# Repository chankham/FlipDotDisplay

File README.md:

# FlipDotDisplay
Code for flip dot display

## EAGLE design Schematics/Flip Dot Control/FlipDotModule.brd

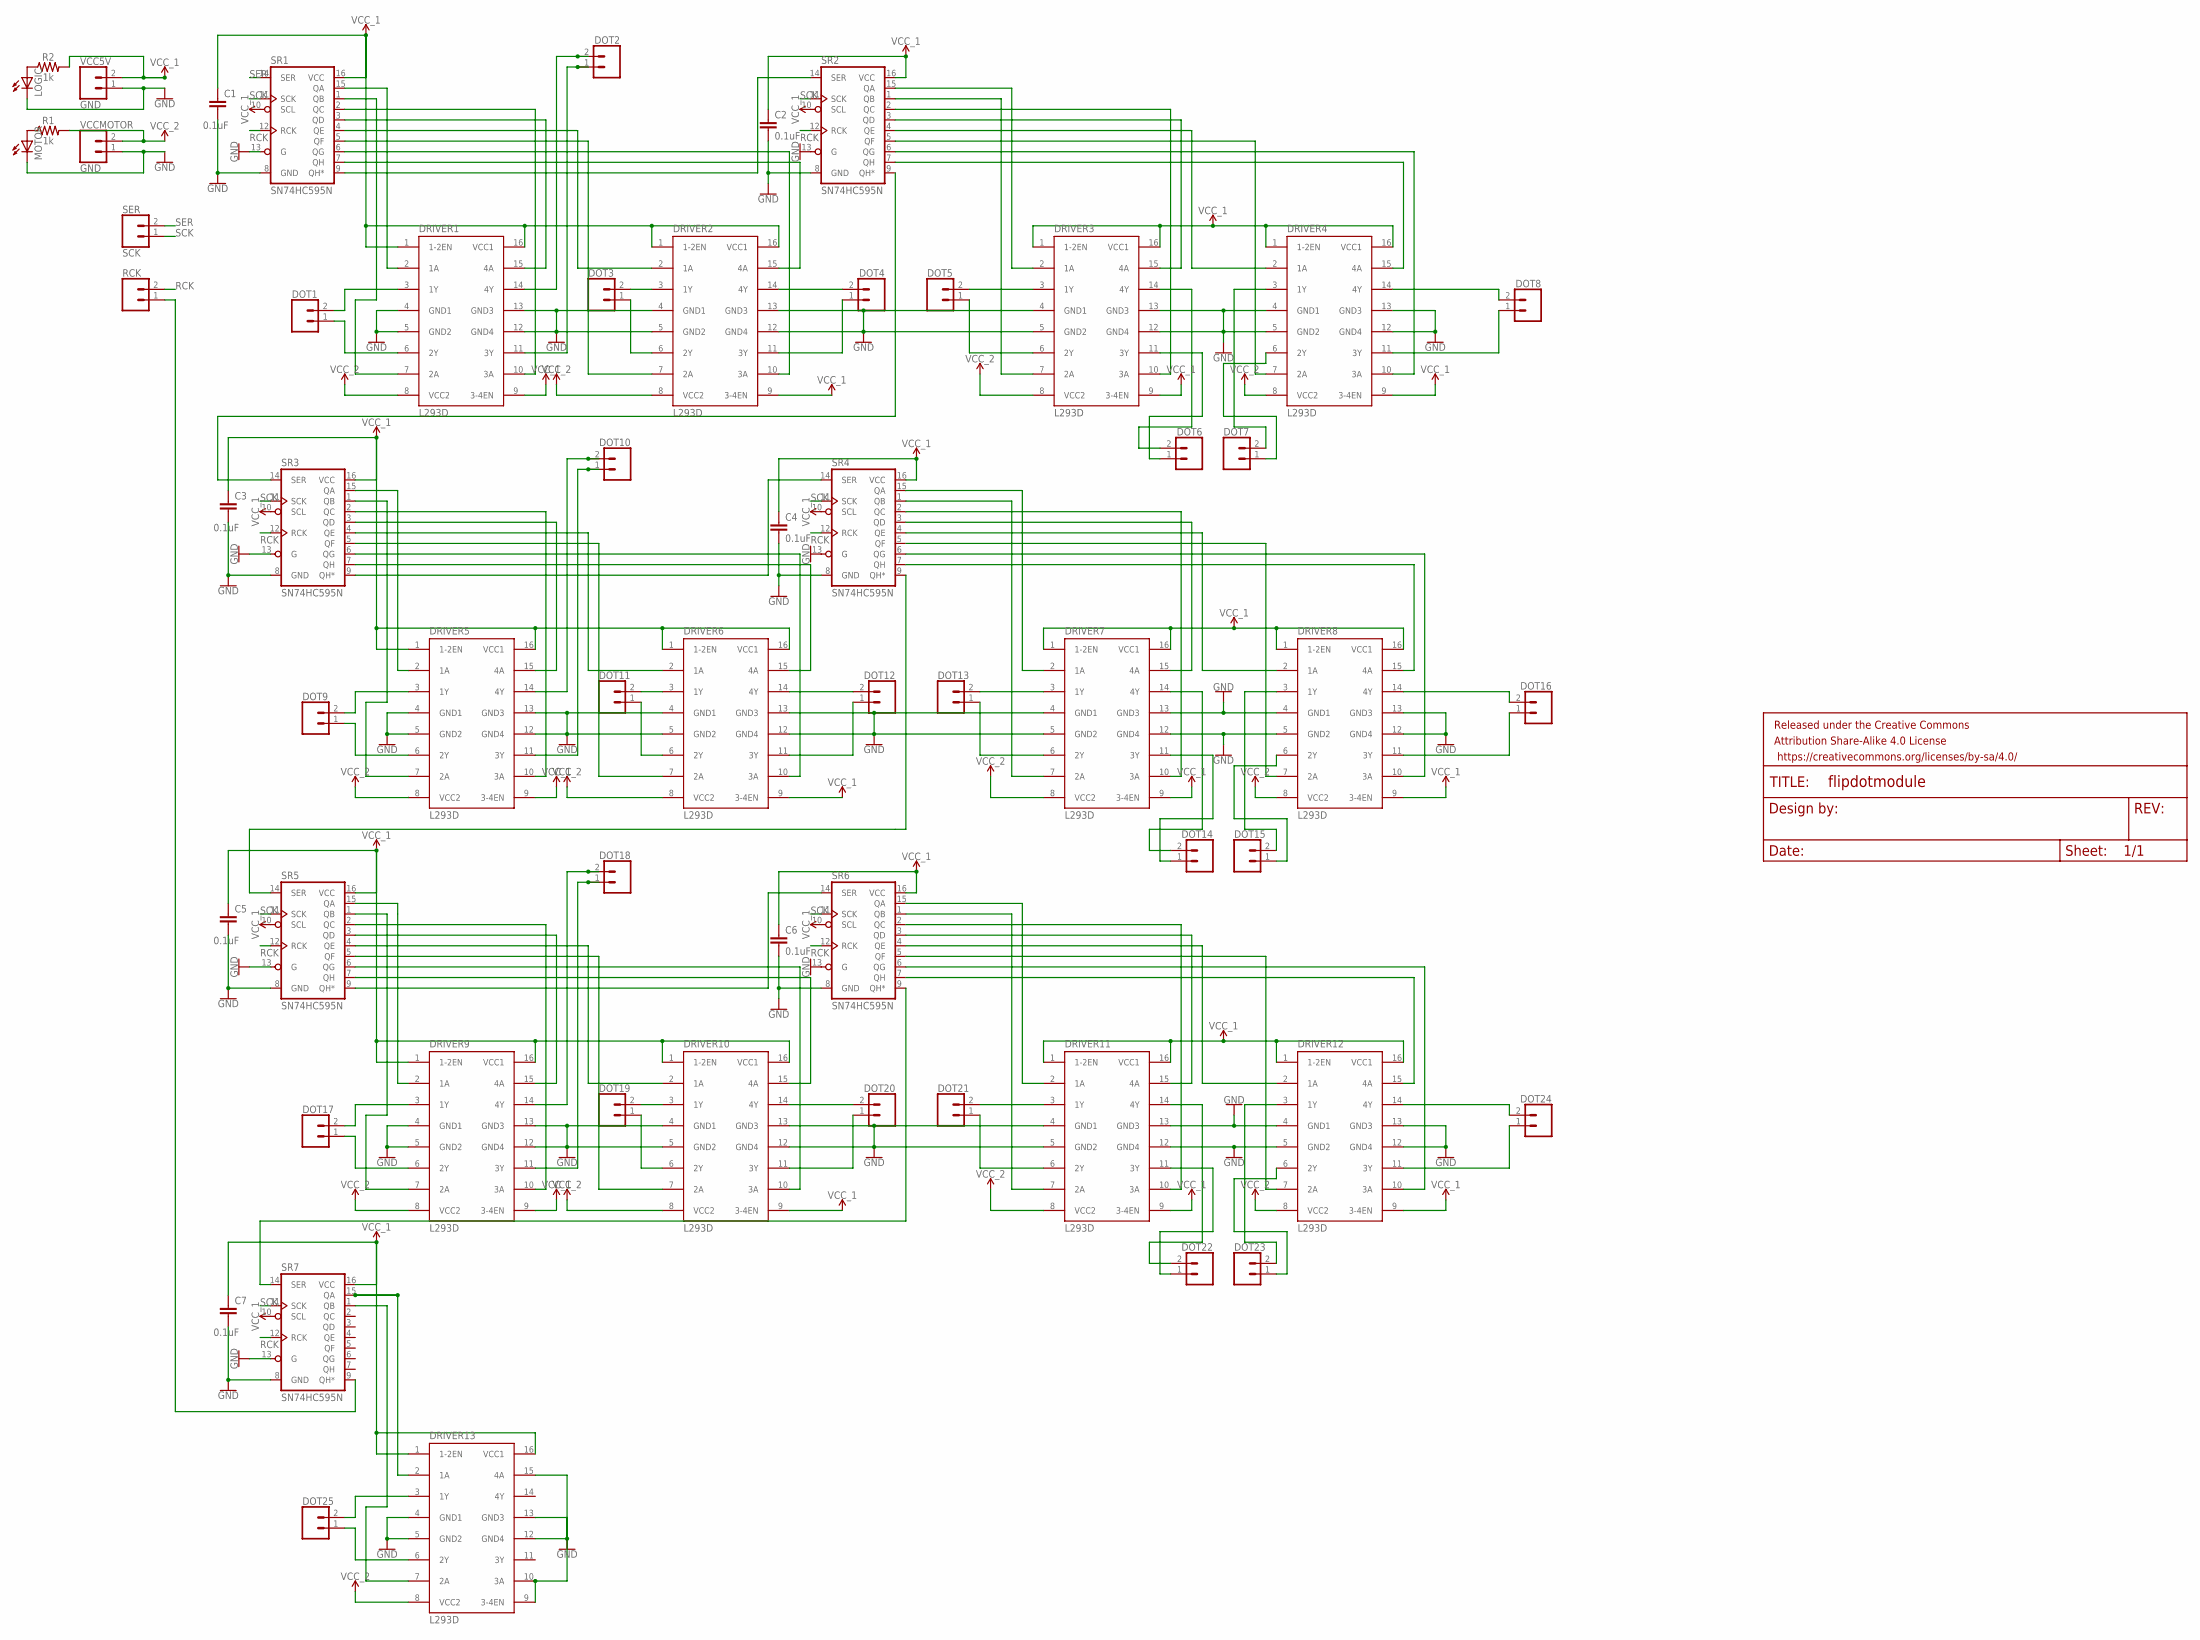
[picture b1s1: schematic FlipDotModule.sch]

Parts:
C1, C2, C3, C4, C5, C6, C7: 0.1uF; CAP-PTH-SMALL-KIT
DOT1, DOT2, DOT3, DOT4, DOT5, DOT6, DOT7, DOT8, DOT9, DOT10, DOT11, DOT12, DOT13, DOT14, DOT15, DOT16, DOT17, DOT18, DOT19, DOT20, DOT21, DOT22, DOT23, DOT24, DOT25: CONN_025MM; SCREWTERMINAL-5MM-2
DRIVER1, DRIVER2, DRIVER3, DRIVER4, DRIVER5, DRIVER6, DRIVER7, DRIVER8, DRIVER9, DRIVER10, DRIVER11, DRIVER12, DRIVER13: L293D; DIL16
FRAME1: FRAME-LETTERNO_PACKAGE; DUMMY
LOGIC: LED3MM
MOTOR: LED3MM
R1, R2: 1k; AXIAL-0.3
RCK: CONN_025MM; SCREWTERMINAL-5MM-2
SER: SCK; SCREWTERMINAL-5MM-2
SR1, SR2, SR3, SR4, SR5, SR6, SR7: SN74HC595N; DIP16
VCC5V: GND; SCREWTERMINAL-5MM-2
VCCMOTOR: GND; SCREWTERMINAL-5MM-2

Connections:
GND: C1.2, C2.2, C3.2, C4.2, C5.2, C6.2, C7.2, DRIVER1.4 (GND1), DRIVER1.5 (GND2), DRIVER1.12 (GND4), DRIVER1.13 (GND3), DRIVER2.4 (GND1), DRIVER2.5 (GND2), DRIVER2.12 (GND4), DRIVER2.13 (GND3), DRIVER3.4 (GND1), DRIVER3.5 (GND2), DRIVER3.12 (GND4), DRIVER3.13 (GND3), DRIVER4.4 (GND1), DRIVER4.5 (GND2), DRIVER4.12 (GND4), DRIVER4.13 (GND3), DRIVER5.4 (GND1), DRIVER5.5 (GND2), DRIVER5.12 (GND4), DRIVER5.13 (GND3), DRIVER6.4 (GND1), DRIVER6.5 (GND2), DRIVER6.12 (GND4), DRIVER6.13 (GND3), DRIVER7.4 (GND1), DRIVER7.5 (GND2), DRIVER7.12 (GND4), DRIVER7.13 (GND3), DRIVER8.4 (GND1), DRIVER8.5 (GND2), DRIVER8.12 (GND4), DRIVER8.13 (GND3), DRIVER9.4 (GND1), DRIVER9.5 (GND2), DRIVER9.12 (GND4), DRIVER9.13 (GND3), DRIVER10.4 (GND1), DRIVER10.5 (GND2), DRIVER10.12 (GND4), DRIVER10.13 (GND3), DRIVER11.4 (GND1), DRIVER11.5 (GND2), DRIVER11.12 (GND4), DRIVER11.13 (GND3), DRIVER12.4 (GND1), DRIVER12.5 (GND2), DRIVER12.12 (GND4), DRIVER12.13 (GND3), DRIVER13.4 (GND1), DRIVER13.5 (GND2), DRIVER13.9 (3-4EN), DRIVER13.10 (3A), DRIVER13.12 (GND4), DRIVER13.13 (GND3), DRIVER13.15 (4A), LOGIC.K (C), MOTOR.K (C), SR1.8 (GND), SR1.13 (G), SR2.8 (GND), SR2.13 (G), SR3.8 (GND), SR3.13 (G), SR4.8 (GND), SR4.13 (G), SR5.8 (GND), SR5.13 (G), SR6.8 (GND), SR6.13 (G), SR7.8 (GND), SR7.13 (G), VCC5V.1, VCCMOTOR.1
unnamed: SR1.9 (QH*), SR2.14 (SER)
unnamed: DOT5.2, DRIVER3.3 (1Y)
unnamed: MOTOR.A, R1.P$1 (1)
unnamed: DRIVER1.7 (2A), SR1.1 (QB)
unnamed: SR3.9 (QH*), SR4.14 (SER)
unnamed: LOGIC.A, R2.P$1 (1)
unnamed: DRIVER1.10 (3A), SR1.2 (QC)
unnamed: DRIVER1.15 (4A), SR1.3 (QD)
unnamed: DRIVER2.2 (1A), SR1.4 (QE)
unnamed: DRIVER2.7 (2A), SR1.5 (QF)
unnamed: DRIVER2.10 (3A), SR1.6 (QG)
unnamed: DRIVER2.15 (4A), SR1.7 (QH)
unnamed: DRIVER1.2 (1A), SR1.15 (QA)
unnamed: DRIVER5.7 (2A), SR3.1 (QB)
unnamed: DRIVER3.2 (1A), SR2.15 (QA)
unnamed: DRIVER3.7 (2A), SR2.1 (QB)
unnamed: DRIVER3.10 (3A), SR2.2 (QC)
unnamed: DRIVER3.15 (4A), SR2.3 (QD)
unnamed: DRIVER4.2 (1A), SR2.4 (QE)
unnamed: DRIVER4.7 (2A), SR2.5 (QF)
unnamed: DRIVER4.10 (3A), SR2.6 (QG)
unnamed: DRIVER4.15 (4A), SR2.7 (QH)
unnamed: DOT1.2, DRIVER1.3 (1Y)
unnamed: DOT4.2, DRIVER2.14 (4Y)
unnamed: DOT2.1, DRIVER1.11 (3Y)
unnamed: DOT1.1, DRIVER1.6 (2Y)
unnamed: DOT3.2, DRIVER2.3 (1Y)
unnamed: DOT3.1, DRIVER2.6 (2Y)
unnamed: DOT2.2, DRIVER1.14 (4Y)
unnamed: DOT4.1, DRIVER2.11 (3Y)
unnamed: DOT5.1, DRIVER3.6 (2Y)
unnamed: DOT6.2, DRIVER3.14 (4Y)
unnamed: DOT6.1, DRIVER3.11 (3Y)
unnamed: DOT7.2, DRIVER4.3 (1Y)
unnamed: DOT7.1, DRIVER4.6 (2Y)
unnamed: DOT8.2, DRIVER4.14 (4Y)
unnamed: DOT8.1, DRIVER4.11 (3Y)
unnamed: DRIVER5.10 (3A), SR3.2 (QC)
unnamed: DRIVER5.15 (4A), SR3.3 (QD)
unnamed: DRIVER6.2 (1A), SR3.4 (QE)
unnamed: DRIVER6.7 (2A), SR3.5 (QF)
unnamed: DRIVER6.10 (3A), SR3.6 (QG)
unnamed: DRIVER6.15 (4A), SR3.7 (QH)
unnamed: DRIVER5.2 (1A), SR3.15 (QA)
unnamed: DRIVER7.2 (1A), SR4.15 (QA)
unnamed: DRIVER7.7 (2A), SR4.1 (QB)
unnamed: DRIVER7.10 (3A), SR4.2 (QC)
unnamed: DRIVER7.15 (4A), SR4.3 (QD)
unnamed: DRIVER8.2 (1A), SR4.4 (QE)
unnamed: DRIVER8.7 (2A), SR4.5 (QF)
unnamed: DRIVER8.10 (3A), SR4.6 (QG)
unnamed: DRIVER8.15 (4A), SR4.7 (QH)
unnamed: DOT10.1, DRIVER5.11 (3Y)
unnamed: DOT9.2, DRIVER5.3 (1Y)
unnamed: DOT9.1, DRIVER5.6 (2Y)
unnamed: DOT11.2, DRIVER6.3 (1Y)
unnamed: DOT11.1, DRIVER6.6 (2Y)
unnamed: DOT10.2, DRIVER5.14 (4Y)
unnamed: DOT12.2, DRIVER6.14 (4Y)
unnamed: DOT12.1, DRIVER6.11 (3Y)
unnamed: DOT13.2, DRIVER7.3 (1Y)
unnamed: DOT13.1, DRIVER7.6 (2Y)
unnamed: DOT14.2, DRIVER7.14 (4Y)
unnamed: DOT14.1, DRIVER7.11 (3Y)
unnamed: DOT15.2, DRIVER8.3 (1Y)
unnamed: DOT15.1, DRIVER8.6 (2Y)
unnamed: DOT16.2, DRIVER8.14 (4Y)
unnamed: DOT16.1, DRIVER8.11 (3Y)
unnamed: SR5.9 (QH*), SR6.14 (SER)
unnamed: DRIVER9.2 (1A), SR5.15 (QA)
unnamed: DRIVER9.7 (2A), SR5.1 (QB)
unnamed: DRIVER9.10 (3A), SR5.2 (QC)
unnamed: DRIVER9.15 (4A), SR5.3 (QD)
unnamed: DRIVER10.2 (1A), SR5.4 (QE)
unnamed: DRIVER10.7 (2A), SR5.5 (QF)
unnamed: DRIVER10.10 (3A), SR5.6 (QG)
unnamed: DRIVER10.15 (4A), SR5.7 (QH)
unnamed: DRIVER11.2 (1A), SR6.15 (QA)
unnamed: DRIVER11.7 (2A), SR6.1 (QB)
unnamed: DRIVER11.10 (3A), SR6.2 (QC)
unnamed: DRIVER11.15 (4A), SR6.3 (QD)
unnamed: DRIVER12.2 (1A), SR6.4 (QE)
unnamed: DRIVER12.7 (2A), SR6.5 (QF)
unnamed: DRIVER12.10 (3A), SR6.6 (QG)
unnamed: DRIVER12.15 (4A), SR6.7 (QH)
unnamed: DOT18.1, DRIVER9.11 (3Y)
unnamed: DOT17.2, DRIVER9.3 (1Y)
unnamed: DOT17.1, DRIVER9.6 (2Y)
unnamed: DOT19.2, DRIVER10.3 (1Y)
unnamed: DOT19.1, DRIVER10.6 (2Y)
unnamed: DOT18.2, DRIVER9.14 (4Y)
unnamed: DOT20.2, DRIVER10.14 (4Y)
unnamed: DOT20.1, DRIVER10.11 (3Y)
unnamed: DOT21.2, DRIVER11.3 (1Y)
unnamed: DOT21.1, DRIVER11.6 (2Y)
unnamed: DOT22.2, DRIVER11.14 (4Y)
unnamed: DOT22.1, DRIVER11.11 (3Y)
unnamed: DOT23.2, DRIVER12.3 (1Y)
unnamed: DOT23.1, DRIVER12.6 (2Y)
unnamed: DOT24.2, DRIVER12.14 (4Y)
unnamed: DOT24.1, DRIVER12.11 (3Y)
unnamed: RCK.1, SR7.9 (QH*)
unnamed: DRIVER13.2 (1A), SR7.15 (QA)
unnamed: DRIVER13.7 (2A), SR7.1 (QB)
unnamed: DOT25.2, DRIVER13.3 (1Y)
unnamed: DOT25.1, DRIVER13.6 (2Y)
unnamed: SR2.9 (QH*), SR3.14 (SER)
unnamed: SR4.9 (QH*), SR5.14 (SER)
unnamed: SR6.9 (QH*), SR7.14 (SER)
RCK: RCK.2, SR1.12 (RCK), SR2.12 (RCK), SR3.12 (RCK), SR4.12 (RCK), SR5.12 (RCK), SR6.12 (RCK), SR7.12 (RCK)
SCK: SER.1, SR1.11 (SCK), SR2.11 (SCK), SR3.11 (SCK), SR4.11 (SCK), SR5.11 (SCK), SR6.11 (SCK), SR7.11 (SCK)
SER: SER.2, SR1.14 (SER)
VCC_1: C1.1, C2.1, C3.1, C4.1, C5.1, C6.1, C7.1, DRIVER1.1 (1-2EN), DRIVER1.9 (3-4EN), DRIVER1.16 (VCC1), DRIVER2.1 (1-2EN), DRIVER2.9 (3-4EN), DRIVER2.16 (VCC1), DRIVER3.1 (1-2EN), DRIVER3.9 (3-4EN), DRIVER3.16 (VCC1), DRIVER4.1 (1-2EN), DRIVER4.9 (3-4EN), DRIVER4.16 (VCC1), DRIVER5.1 (1-2EN), DRIVER5.9 (3-4EN), DRIVER5.16 (VCC1), DRIVER6.1 (1-2EN), DRIVER6.9 (3-4EN), DRIVER6.16 (VCC1), DRIVER7.1 (1-2EN), DRIVER7.9 (3-4EN), DRIVER7.16 (VCC1), DRIVER8.1 (1-2EN), DRIVER8.9 (3-4EN), DRIVER8.16 (VCC1), DRIVER9.1 (1-2EN), DRIVER9.9 (3-4EN), DRIVER9.16 (VCC1), DRIVER10.1 (1-2EN), DRIVER10.9 (3-4EN), DRIVER10.16 (VCC1), DRIVER11.1 (1-2EN), DRIVER11.9 (3-4EN), DRIVER11.16 (VCC1), DRIVER12.1 (1-2EN), DRIVER12.9 (3-4EN), DRIVER12.16 (VCC1), DRIVER13.1 (1-2EN), DRIVER13.16 (VCC1), R2.P$2 (2), SR1.10 (SCL), SR1.16 (VCC), SR2.10 (SCL), SR2.16 (VCC), SR3.10 (SCL), SR3.16 (VCC), SR4.10 (SCL), SR4.16 (VCC), SR5.10 (SCL), SR5.16 (VCC), SR6.10 (SCL), SR6.16 (VCC), SR7.10 (SCL), SR7.16 (VCC), VCC5V.2
VCC_2: DRIVER1.8 (VCC2), DRIVER2.8 (VCC2), DRIVER3.8 (VCC2), DRIVER4.8 (VCC2), DRIVER5.8 (VCC2), DRIVER6.8 (VCC2), DRIVER7.8 (VCC2), DRIVER8.8 (VCC2), DRIVER9.8 (VCC2), DRIVER10.8 (VCC2), DRIVER11.8 (VCC2), DRIVER12.8 (VCC2), DRIVER13.8 (VCC2), R1.P$2 (2), VCCMOTOR.2

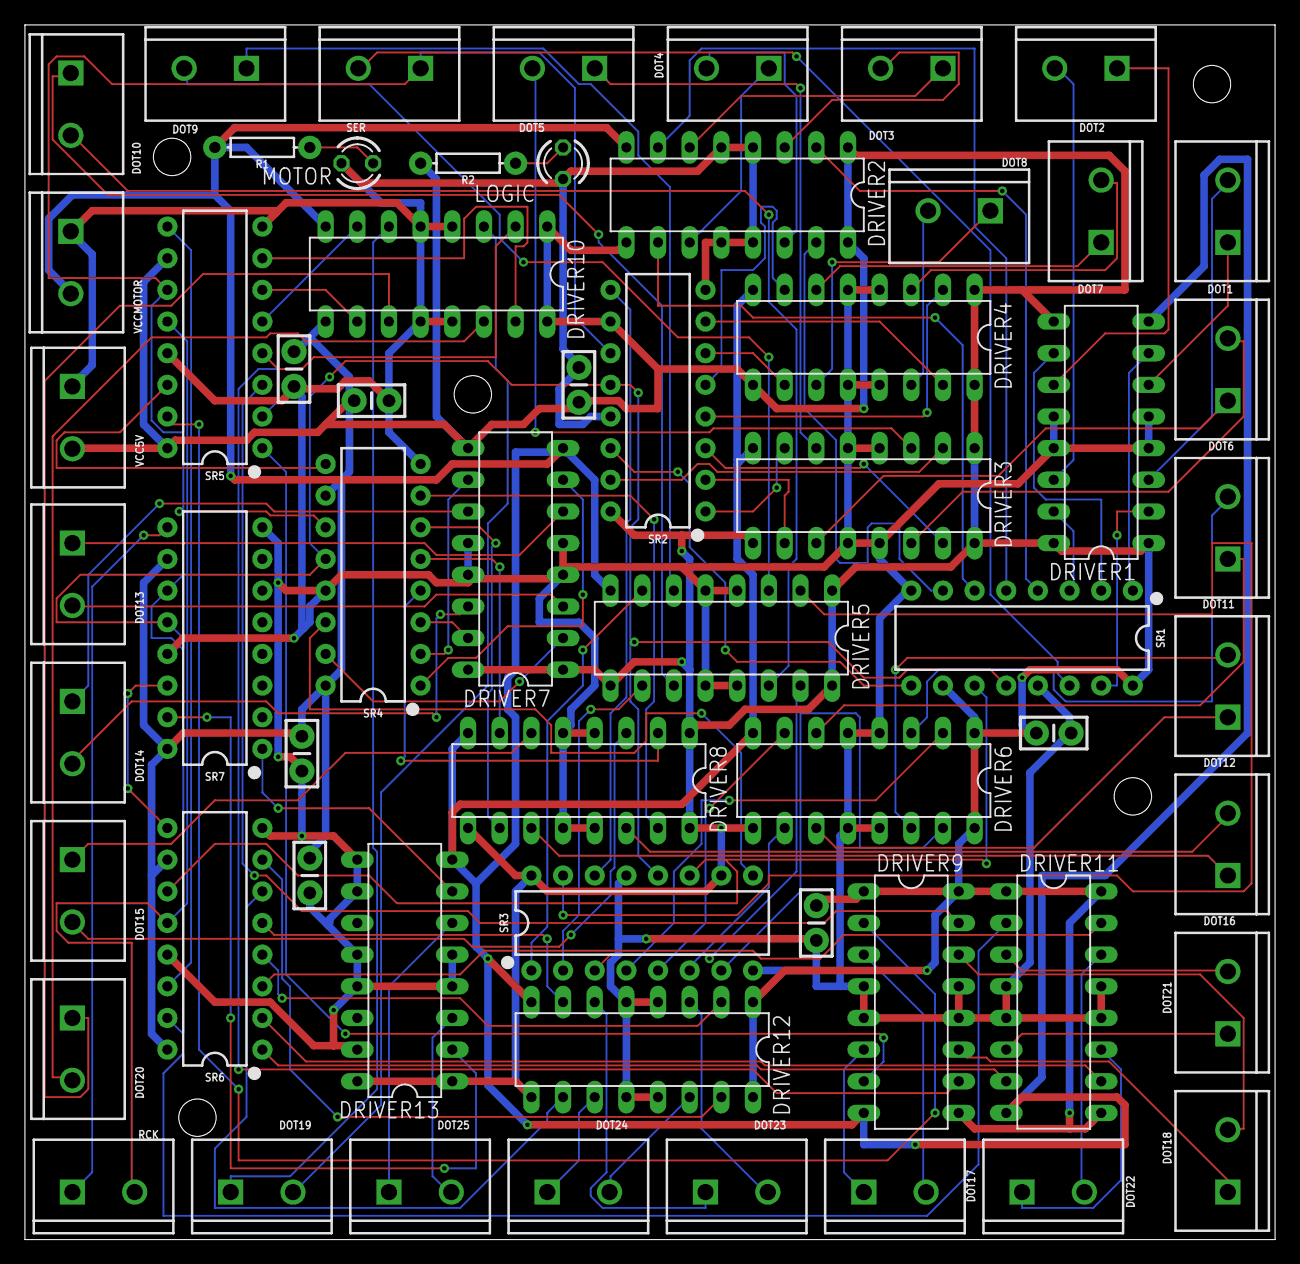
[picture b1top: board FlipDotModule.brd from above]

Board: 2 copper layers, 100.3 x 97.5 mm, 61 parts (0 on the bottom side), 115 nets.

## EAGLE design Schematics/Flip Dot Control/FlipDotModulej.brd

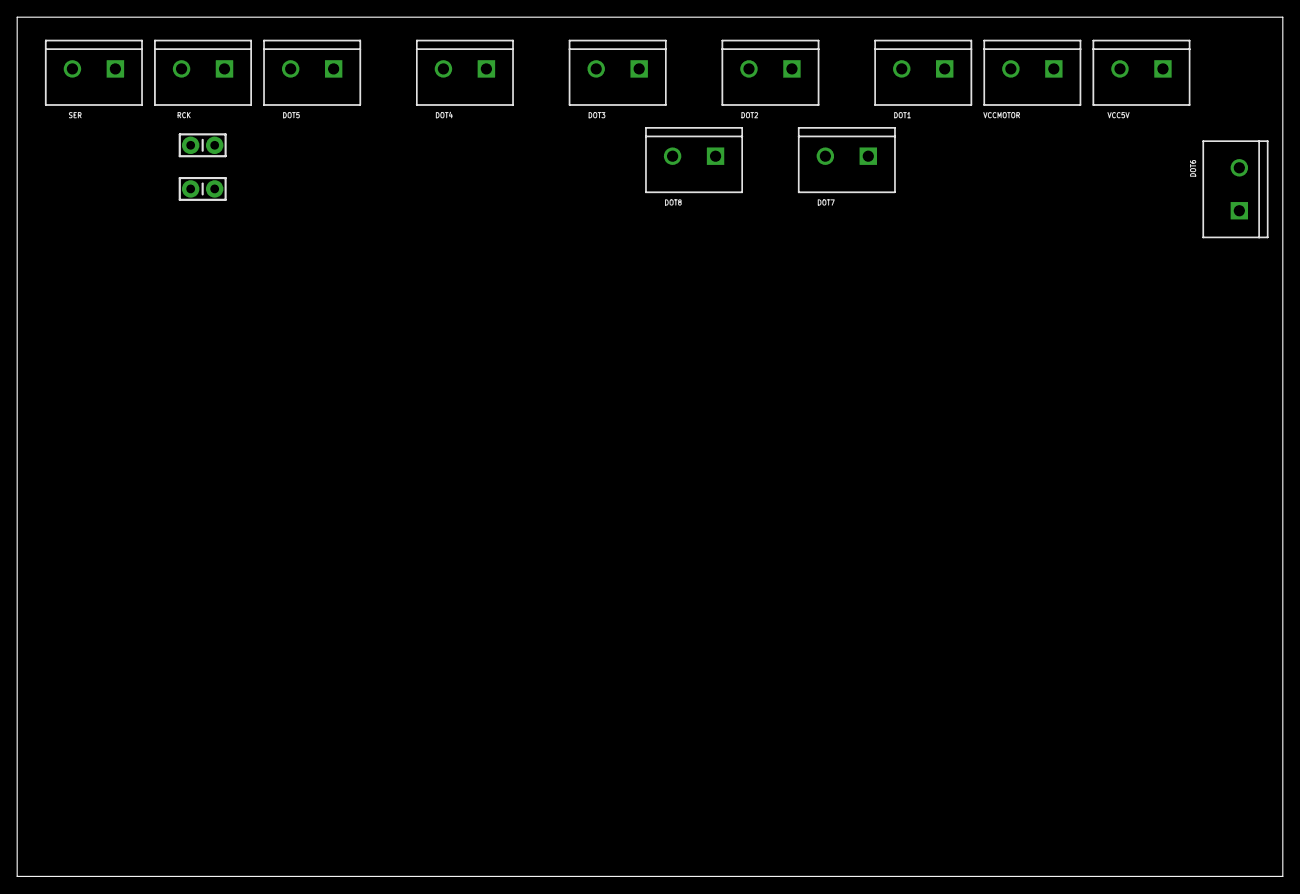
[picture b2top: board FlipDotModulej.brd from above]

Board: 2 copper layers, 147.3 x 100.0 mm, 15 parts (0 on the bottom side), 2 nets, no tracks yet.

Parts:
C1, C2: 0.1uF; CAP-PTH-SMALL-KIT
DOT1, DOT2, DOT3, DOT4, DOT5, DOT6, DOT7, DOT8: SCREWTERMINAL-5MM-2
FRAME1: FRAME-LETTERNO_PACKAGE; DUMMY
RCK: SCREWTERMINAL-5MM-2
SER: SCK; SCREWTERMINAL-5MM-2
VCC5V: GND; SCREWTERMINAL-5MM-2
VCCMOTOR: GND; SCREWTERMINAL-5MM-2

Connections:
GND: C1.2, C2.2, RCK.1, VCC5V.1, VCCMOTOR.1
VCC_1: C1.1, C2.1, VCC5V.2

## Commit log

2018-11-09 First Commit (uploading files)
2018-11-09 Uploaded Arduino Code
2018-11-09 Uploaded 3D models
2018-11-09 Added Library
2018-11-12 Uploading testing part
2018-11-25 Updates and new features
2018-12-02 Working 10 at a time
2018-12-03 10 at a trime
2018-12-03 Revert "10 at a trime"
    This reverts commit 5a991e7d1f35823cbbe2945a833c8ba885e8fbf7.
2018-12-03 latest work 2 window 1 arduino
2018-12-11 Rasp Pi Push

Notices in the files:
parts and their libraries:
SparkFun-Capacitors: Licensing: Creative Commons ShareAlike 4.0 International - https://creativecommons.org/licenses/by-sa/4.0
SparkFun-Aesthetics: Released under the Creative Commons Attribution Share-Alike 4.0 License
SparkFun-Aesthetics: https://creativecommons.org/licenses/by-sa/4.0
